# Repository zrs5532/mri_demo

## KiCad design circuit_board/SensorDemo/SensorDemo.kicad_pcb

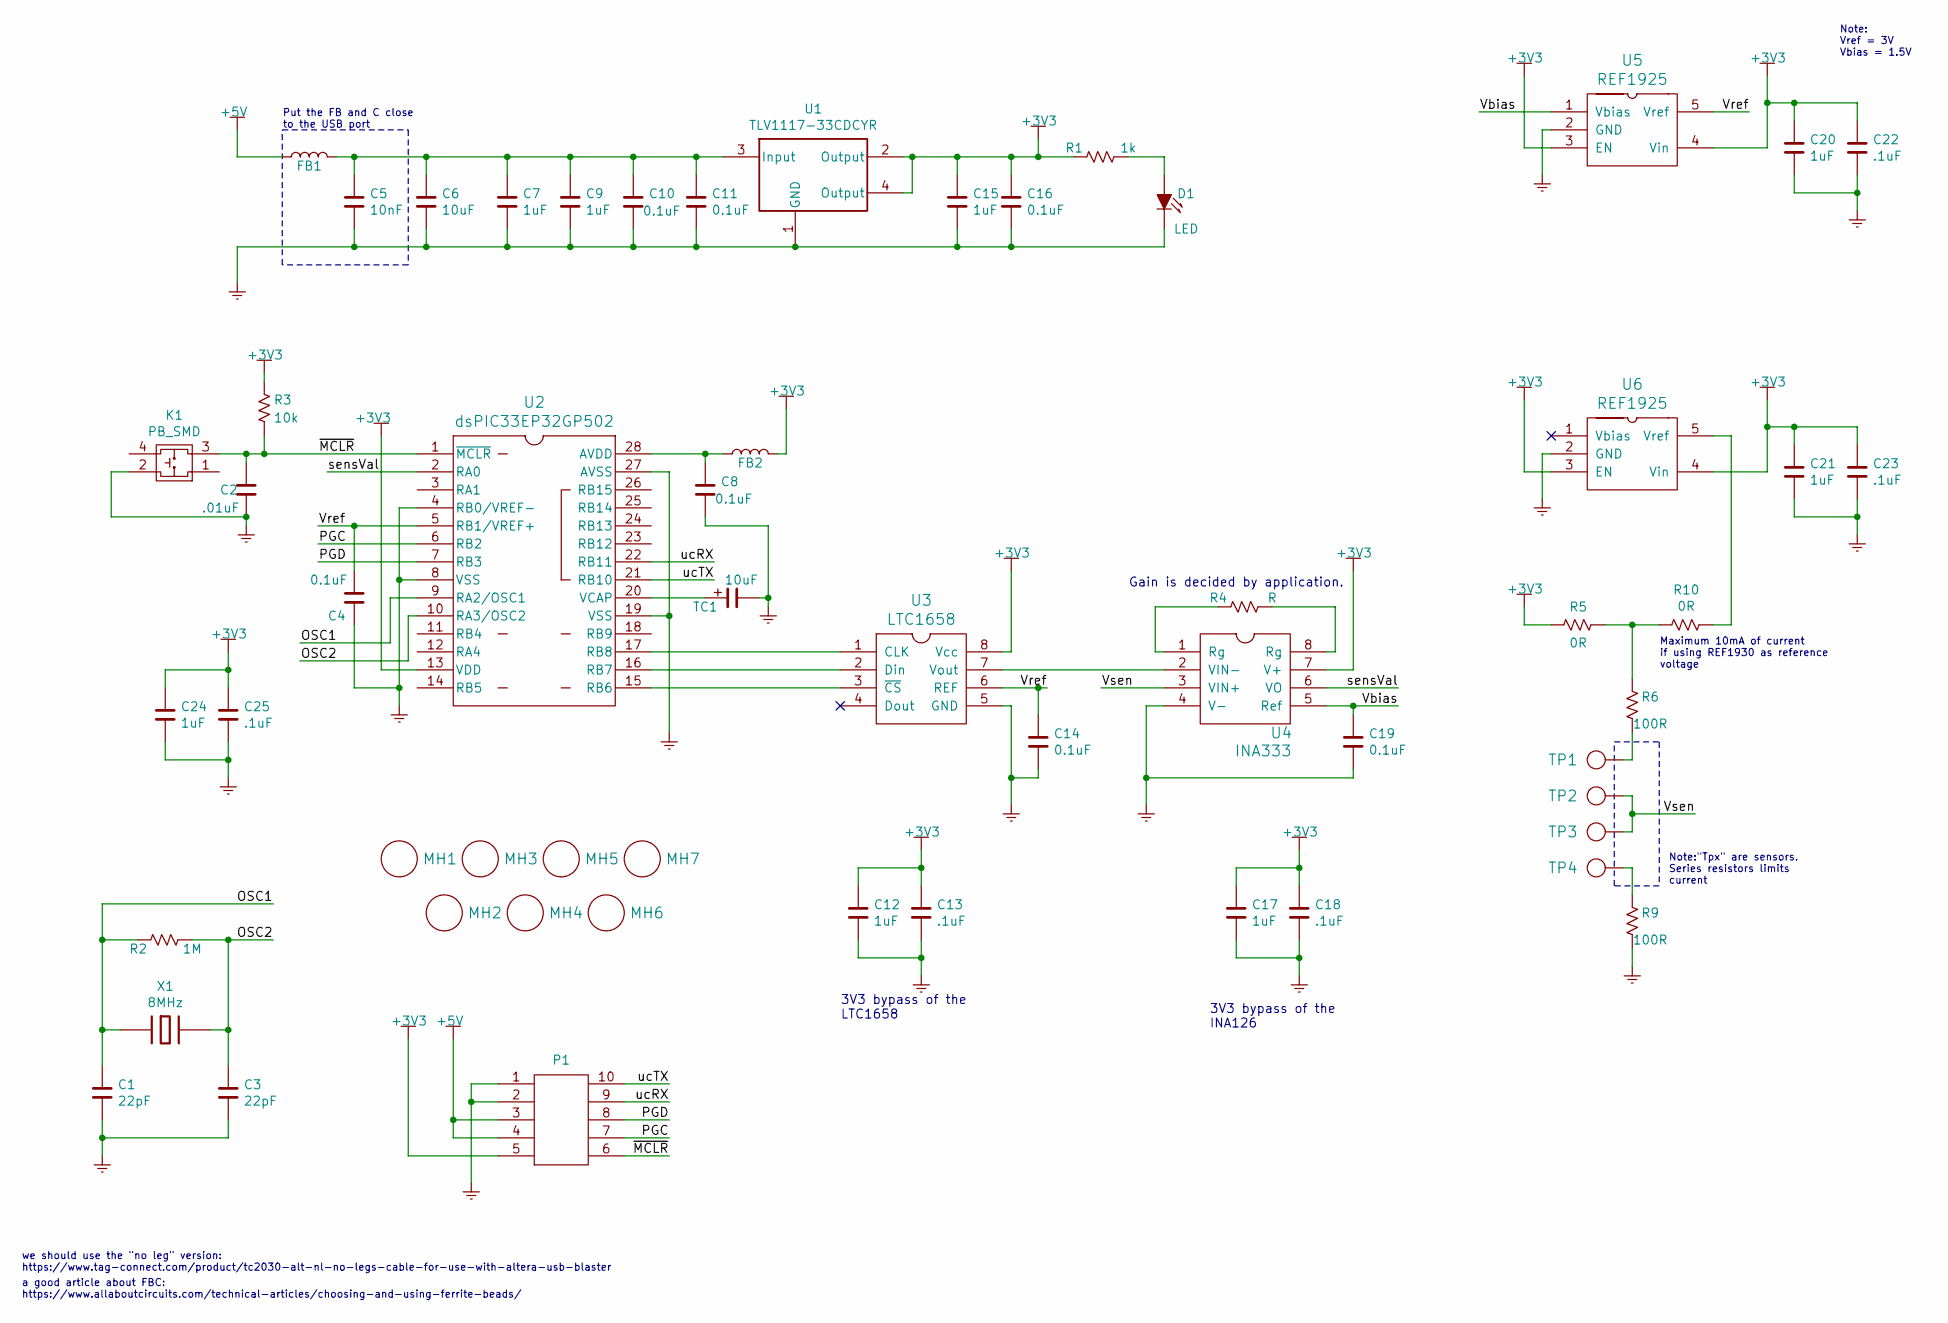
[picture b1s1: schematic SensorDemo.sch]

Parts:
C1, C3: 22pF; C0805
C2: .01uF; C0805
C4, C8, C10, C11, C14, C16, C19: 0.1uF; C0805
C5: 10nF; C0805
C6: 10uF; C0805
C7, C9, C12, C15, C17, C20, C21, C24: 1uF; C0805
C13, C18, C22, C23, C25: .1uF; C0805
D1: LED; LED0805
FB1, FB2: 12.3071 nano ohm; R0805
K1: PB_SMD; Key_SMD
MH1, MH2, MH3, MH4, MH5, MH6, MH7: MH; MH_3MM
P1: TC2050_IDC_NL; TC2050
R1: 1k; R0805
R2: 1M; R0805
R3: 10k; R0805
R4: R; R0805
R5, R10: 0R; R0805
R6, R9: 100R; R0805
TC1: 10uF; C1210
TP1, TP2, TP3, TP4: TP; TP_SMD_2MM
U1: TLV1117-33CDCYR; SOT-223
U2: dsPIC33EP32GP502; SOIC-28
U3: LTC1658; SOIC-8
U4: INA333; MSOP-8
U5, U6: REF1925; SOT-23-5
X1: 8MHz; CRYSTAL_ABM3-8.000MHz-D2Y-T

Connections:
+3V3: C12.1, C13.1, C15.1, C16.1, C17.1, C18.1, C20.1, C21.1, C22.1, C23.1, C24.1, C25.1, FB2.2, P1.5, R1.1, R3.1, R5.1, U1.2 (Output), U1.4 (Output), U2.13 (VDD), U3.8 (Vcc), U4.7 (V+), U5.3 (EN), U5.4 (Vin), U6.3 (EN), U6.4 (Vin); also elsewhere on the board
+5V: FB1.1, P1.3, P1.4; also elsewhere on the board
/OSC1: C1.1, R2.1, U2.9 (RA2/OSC1), X1.1
/OSC2: C3.1, R2.2, U2.10 (RA3/OSC2), X1.2
/PGC: P1.7, U2.6 (RB2)
/PGD: P1.8, U2.7 (RB3)
/Vbias: C19.1, U4.5 (Ref), U5.1 (Vbias)
/Vref: C4.1, C14.1, U2.5 (RB1/VREF+), U3.6 (REF), U5.5 (Vref)
/Vsen: TP2.1, TP3.1, U4.3 (VIN+); also elsewhere on the board
/sensVal: U2.2 (RA0), U4.6 (VO); also elsewhere on the board
/ucRX: P1.9, U2.22 (RB11)
/ucTX: P1.10, U2.21 (RB10)
/~MCLR: C2.1, K1.3, P1.6, R3.2, U2.1 (~MCLR)
GND: C1.2, C2.2, C3.2, C4.2, C5.2, C6.2, C7.2, C8.2, C9.2, C10.2, C11.2, C12.2, C13.2, C14.2, C15.2, C16.2, C17.2, C18.2, C19.2, C20.2, C21.2, C22.2, C23.2, C24.2, C25.2, D1.2 (K), K1.2, P1.1, P1.2, R9.2, TC1.2, U1.1 (GND), U2.4 (RB0/VREF-), U2.8 (VSS), U2.19 (VSS), U2.27 (AVSS), U3.5 (GND), U4.4 (V-), U5.2 (GND), U6.2 (GND)
unnamed: C8.1, FB2.1, U2.28 (AVDD)
unnamed: C5.1, C6.1, C7.1, C9.1, C10.1, C11.1, FB1.2, U1.3 (Input)
unnamed: D1.1 (A), R1.2
unnamed: R4.1, U4.1 (Rg)
unnamed: R4.2, U4.8 (Rg)
unnamed: R6.2, TP1.1
unnamed: R9.1, TP4.1
unnamed: R5.2, R6.1, R10.1
unnamed: R10.2, U6.5 (Vref)
unnamed: TC1.1, U2.20 (VCAP)
unnamed: U2.15 (RB6), U3.3 (~CS)
unnamed 25: U2.16 (RB7), U3.2 (Din); also elsewhere on the board
unnamed 26: U2.17 (RB8), U3.1 (CLK); also elsewhere on the board
unnamed 27: U3.7 (Vout), U4.2 (VIN-); also elsewhere on the board

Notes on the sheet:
Note: Vref = 3V Vbias = 1.5V
Put the FB and C close to the USB port
a good article about FBC: https://www.allaboutcircuits.com/technical-articles/choosing-and-using-ferrite-beads/
Gain is decided by application.
3V3 bypass of the LTC1658
3V3 bypass of the INA126
Maximum 10mA of current if using REF1930 as reference voltage
Note:"Tpx" are sensors. Series resistors limits current
we should use the "no leg" version: https://www.tag-connect.com/product/tc2030-alt-nl-no-legs-cable-for-use-with-altera-usb-blaster

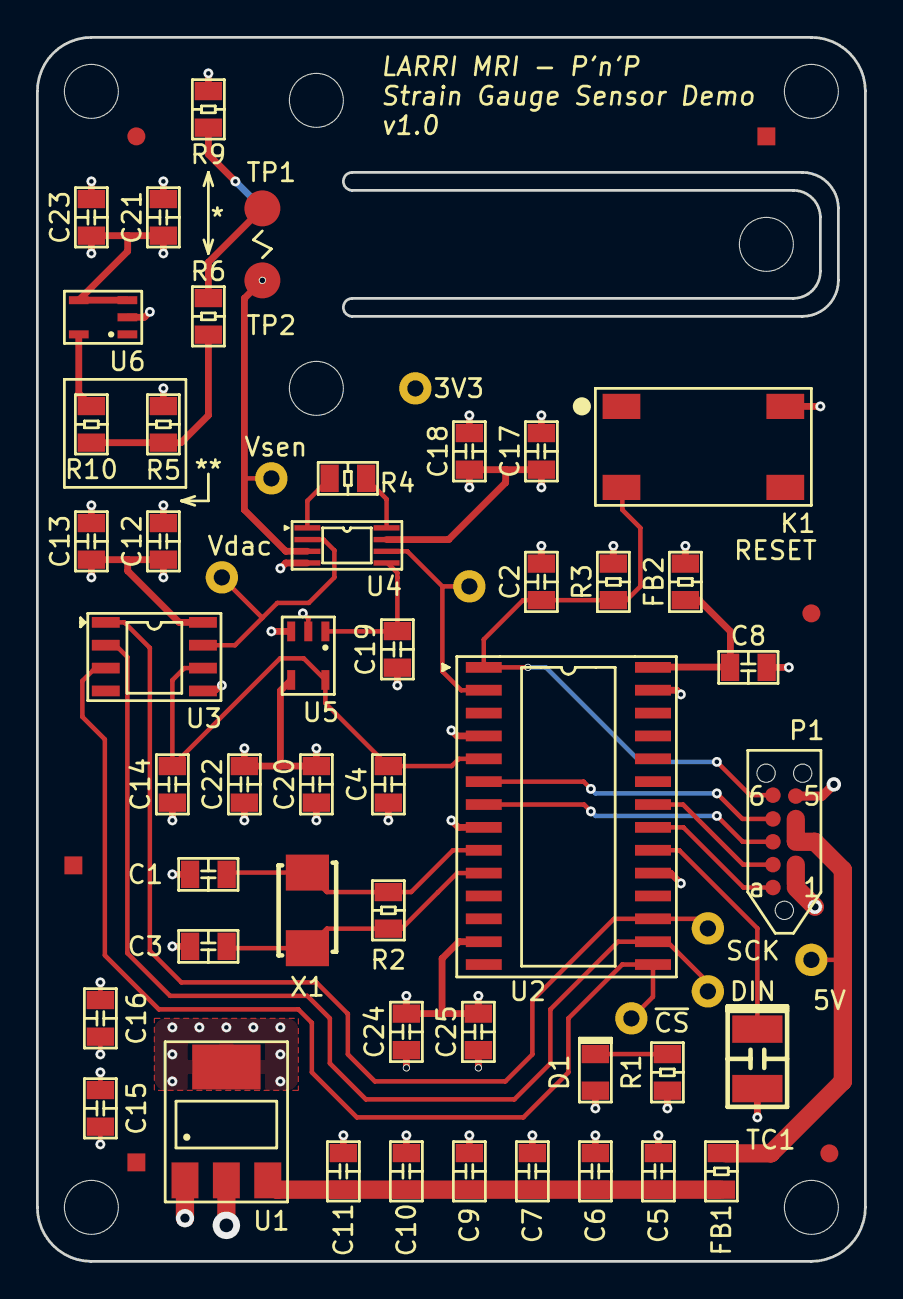
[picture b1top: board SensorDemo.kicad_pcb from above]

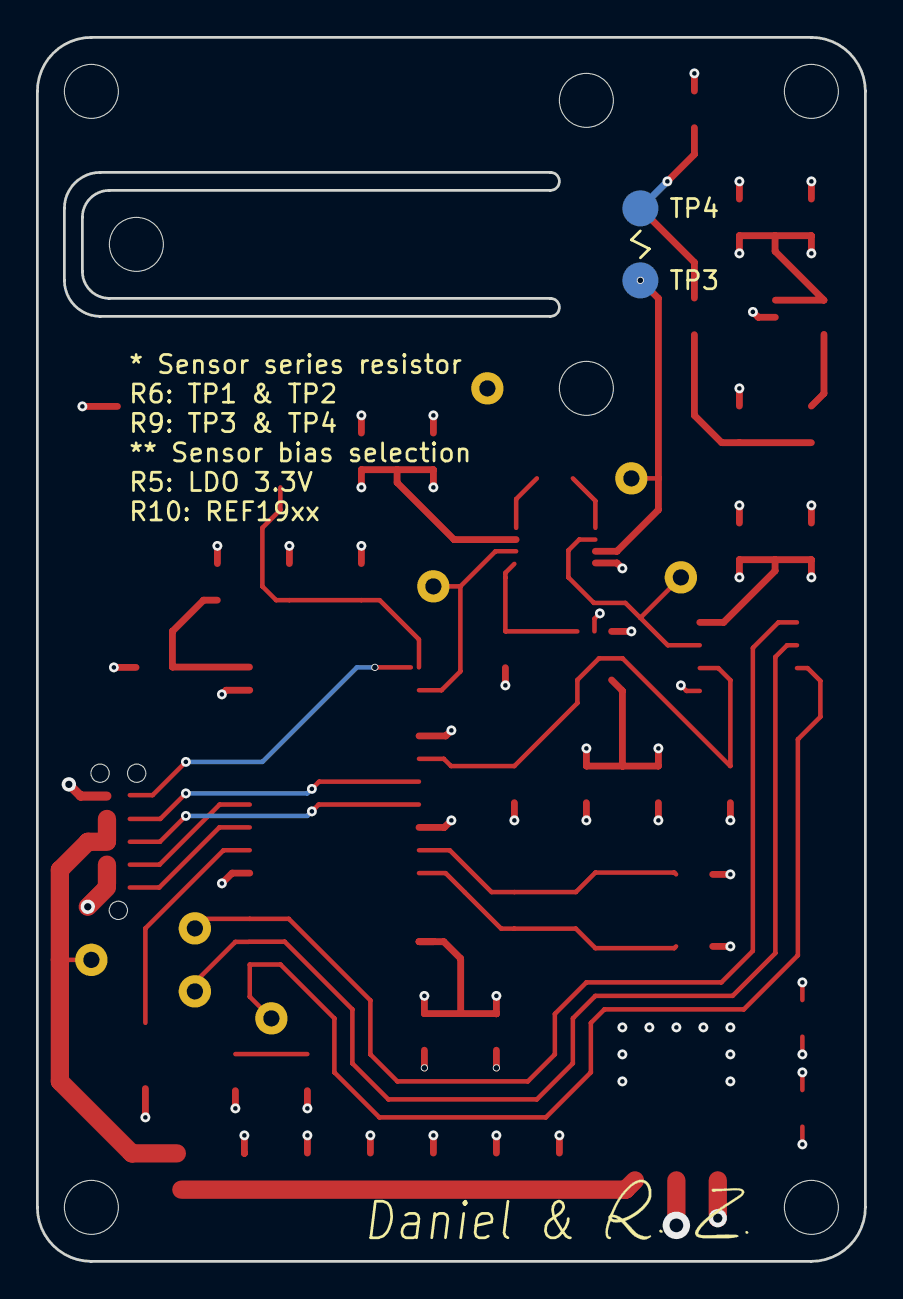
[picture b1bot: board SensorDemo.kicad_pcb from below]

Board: 4 copper layers, 46.0 x 68.0 mm, 70 parts (2 on the bottom side), 28 nets.

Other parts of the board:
3V3, 5V: TP_TH
DIN: TP_TH
FD: Val**; FD_1MM_CR
FD#2, FD#3, FD#5: Val**; FD_1MM_SQ
FD#4, FD#6: Val**; FD_1MM_CR
SCK: TP_TH
Vdac: TP_TH
Vsen: TP_TH
sensVal: TP_TH

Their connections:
+3V3: 3V3.1; also elsewhere on the board
+5V: 5V.1; also elsewhere on the board
/Vsen: Vsen.1; also elsewhere on the board
/sensVal: sensVal.1; also elsewhere on the board
unnamed 25: DIN.1; also elsewhere on the board
unnamed 26: SCK.1; also elsewhere on the board
unnamed 27: Vdac.1; also elsewhere on the board

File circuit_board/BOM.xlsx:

Component | Description | Link | Quantity
C1, C3 | 22pF | https://www.mouser.com/ProductDetail/KEMET/C0805C220K3HACTU?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 | 100
C2, C5, C6 | 0.01uF | https://www.mouser.com/ProductDetail/AVX/08051C103KAT2A?qs=K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 | 100
C4, C8, C10, C11, C13, C14, C16, C18, C19, C22, C23, C25 | 0.1uF | https://www.mouser.com/ProductDetail/AVX/08055C104KAT2A?qs=s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 | 100
C7, C9, C12, C15, C17, C20, C21, C24 | 1uF | https://www.mouser.com/ProductDetail/Samsung-Electro-Mechani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 | 100
FB1, FB2 | 12.3071 nano Ohm | https://www.mouser.com/ProductDetail/Fair-Rite/2508051027Y1?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 | 100
K1 | Push Button | https://www.mouser.com/ProductDetail/E-Switch/LL3301NF065QG/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 | 25
R1 | 1k Ohm | https://www.mouser.com/ProductDetail/Vishay-Dale/CRCW08051K0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 | 100
R2 | 1M Ohm | https://www.mouser.com/ProductDetail/Vishay-Dale/CRCW08051M0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 | 100
R3 | 10k Ohm | https://www.mouser.com/ProductDetail/Bourns/CR0805-FX-1003EL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 | 100
R6, R9 | 100 Ohm | https://www.mouser.com/ProductDetail/Vishay-Dale/CRCW0805100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 | 100
TC1 | 10uF | https://www.mouser.com/ProductDetail/AVX/TAJA106K010RNJV?qs=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 | 20
U1 | LDO - TLV1117-33CDCYR | https://www.mouser.com/ProductDetail/STMicroelectronics/LDL1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 | 20
U2 | dsPIC33EP32GP502 | https://www.mouser.com/ProductDetail/Microchip-Technology/ds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 | 5
U3 | DAC - LTC1659 | https://www.mouser.com/ProductDetail/Analog-Devices/LTC1659C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 | 5
 | LTC 1655L | https://www.mouser.com/ProductDetail/Analog-Devices/LTC1655L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 | 3
 | LED | https://www.mouser.com/ProductDetail/Kingbright/APT2012SRCPR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 | 10
 | 0R | https://www.mouser.com/ProductDetail/Yageo/RC0805JR-070RL?qs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 | 100
 | IDC | https://www.mouser.com/ProductDetail/Wurth-Elektronik/612010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 | 5
 | uart bridge | https://www.mouser.com/ProductDetail/SparkFun/BOB-13263?qs=w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 | 3
 | tag-cable | https://www.tag-connect.com/product/tc2050-idc-nl-10-pin-no-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 | 1
stunts | SOIC8 | https://www.mouser.com/ProductDetail/STMicroelectronics/LM35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 | 10
 | MSOP8 | https://www.mouser.com/ProductDetail/NJR/NJM2904CARB1-TE1?qs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 | 10
 | SOIC28 | https://www.mouser.com/ProductDetail/Microchip-Technology/PI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 | 10
 | SOT23-5 | https://www.mouser.com/ProductDetail/Microchip-Technology-Mi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 | 10
 | SOT223 | https://www.mouser.com/ProductDetail/Nexperia/PMT560ENEAX?qs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 | 10

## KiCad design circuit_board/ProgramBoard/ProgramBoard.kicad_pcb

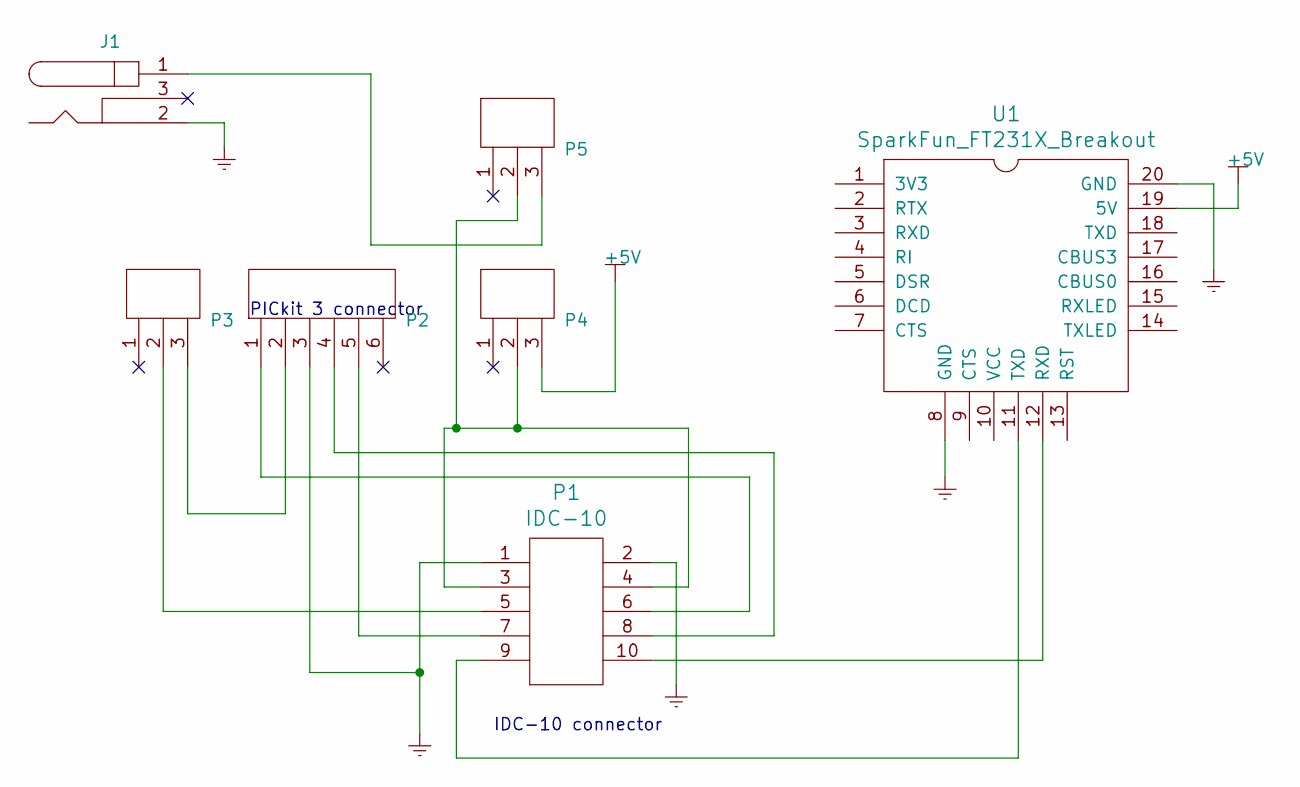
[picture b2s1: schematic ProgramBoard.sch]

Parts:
J1: BARREL_JACK
P1: IDC-10; IDC_10
P2: HEADER_6
P3, P4, P5: HEADER_3
U1: SparkFun_FT231X_Breakout

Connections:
+5V: P4.3, U1.19 (5V)
GND: J1.2, P1.1, P1.2, P2.3, U1.8 (GND), U1.20 (GND)
unnamed: J1.1, P5.3
unnamed: P1.3, P1.4, P4.2, P5.2
unnamed: P1.5, P3.2
unnamed: P1.6, P2.1
unnamed: P1.7, P2.5
unnamed: P1.8, P2.4
unnamed: P1.9, U1.11 (TXD)
unnamed: P1.10, U1.12 (RXD)
unnamed: P2.2, P3.3

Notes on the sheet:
PICkit 3 connector
IDC-10 connector

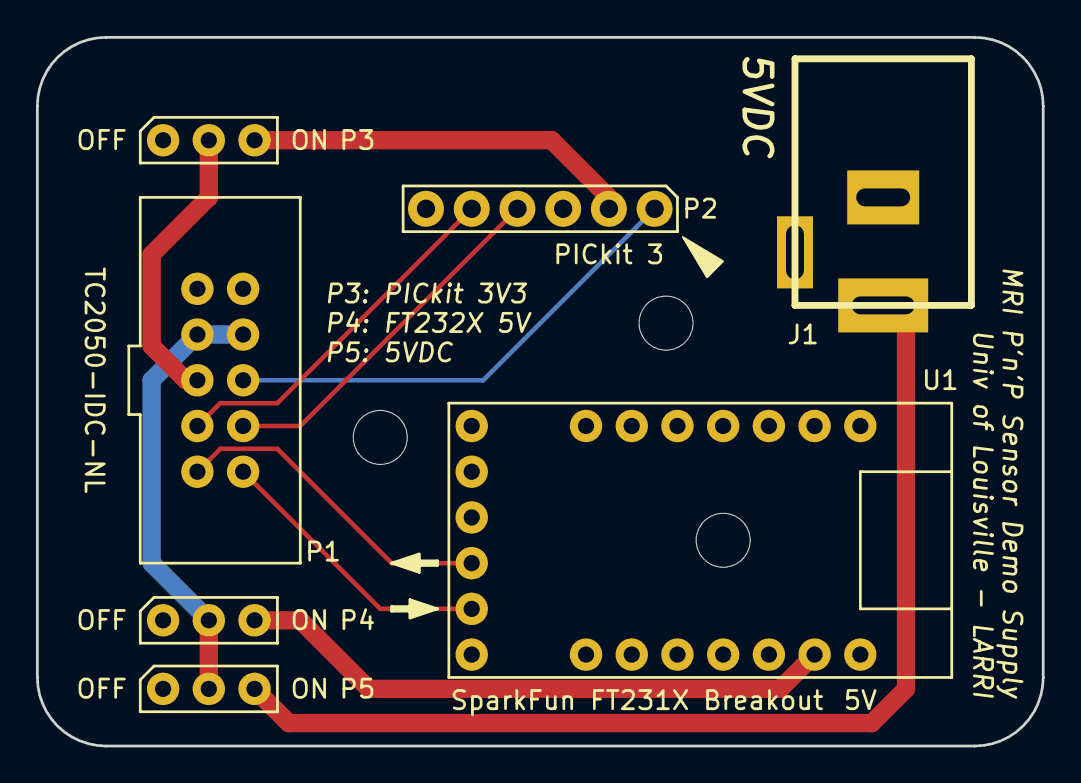
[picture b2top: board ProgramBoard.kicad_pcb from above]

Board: 2 copper layers, 55.9 x 39.4 mm, 10 parts (0 on the bottom side), 11 nets.

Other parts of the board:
MH3, MH3#2, MH3#3: MH; MH_3MM

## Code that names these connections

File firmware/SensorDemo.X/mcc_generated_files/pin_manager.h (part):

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*/
/**
  @Summary
    Sets the GPIO pin, RA0, high using LATA0.

  @Description
    Sets the GPIO pin, RA0, high using LATA0.

  @Preconditions
    The RA0 must be set to an output.
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#define channel_AN0_SetHigh()          (_LATA0 = 1)
/**
  @Summary
    Sets the GPIO pin, RA0, low using LATA0.

  @Description
    Sets the GPIO pin, RA0, low using LATA0.

  @Preconditions
    The RA0 must be set to an output.
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#define channel_AN0_SetLow()           (_LATA0 = 0)
/**
  @Summary
    Toggles the GPIO pin, RA0, using LATA0.

  @Description
    Toggles the GPIO pin, RA0, using LATA0.

  @Preconditions
    The RA0 must be set to an output.
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#define channel_AN0_Toggle()           (_LATA0 ^= 1)
/**
  @Summary
    Reads the value of the GPIO pin, RA0.

  @Description
    Reads the value of the GPIO pin, RA0.

  @Preconditions
    None.
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    </code>

*/
#define channel_AN0_GetValue()         _RA0
/**
  @Summary
    Configures the GPIO pin, RA0, as an input.

  @Description
    Configures the GPIO pin, RA0, as an input.

  @Preconditions
    None.
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#define channel_AN0_SetDigitalInput()  (_TRISA0 = 1)
/**
  @Summary
    Configures the GPIO pin, RA0, as an output.

  @Description
    Configures the GPIO pin, RA0, as an output.

  @Preconditions
    None.
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#define channel_AN0_SetDigitalOutput() (_TRISA0 = 0)
/**
  @Summary
    Sets the GPIO pin, RB6, high using LATB6.

  @Description
    Sets the GPIO pin, RB6, high using LATB6.

  @Preconditions
    The RB6 must be set to an output.
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#define CS1_SetHigh()          (_LATB6 = 1)
/**
  @Summary
    Sets the GPIO pin, RB6, low using LATB6.

  @Description
    Sets the GPIO pin, RB6, low using LATB6.

  @Preconditions
    The RB6 must be set to an output.
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#define CS1_SetLow()           (_LATB6 = 0)
/**
  @Summary
    Toggles the GPIO pin, RB6, using LATB6.

  @Description
    Toggles the GPIO pin, RB6, using LATB6.

  @Preconditions
    The RB6 must be set to an output.
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#define CS1_Toggle()           (_LATB6 ^= 1)
/**
  @Summary
    Reads the value of the GPIO pin, RB6.

  @Description
    Reads the value of the GPIO pin, RB6.

  @Preconditions
    None.
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    </code>

*/
#define CS1_GetValue()         _RB6
/**
  @Summary
    Configures the GPIO pin, RB6, as an input.

  @Description
    Configures the GPIO pin, RB6, as an input.

  @Preconditions
    None.
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#define CS1_SetDigitalInput()  (_TRISB6 = 1)
/**
  @Summary
    Configures the GPIO pin, RB6, as an output.

  @Description
    Configures the GPIO pin, RB6, as an output.

  @Preconditions
    None.
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#define CS1_SetDigitalOutput() (_TRISB6 = 0)
/**
  @Summary
    Sets the GPIO pin, RB7, high using LATB7.

  @Description
    Sets the GPIO pin, RB7, high using LATB7.

  @Preconditions
    The RB7 must be set to an output.
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#define SDO2_SetHigh()          (_LATB7 = 1)
/**
  @Summary
    Sets the GPIO pin, RB7, low using LATB7.

  @Description
    Sets the GPIO pin, RB7, low using LATB7.

  @Preconditions
    The RB7 must be set to an output.
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#define SDO2_SetLow()           (_LATB7 = 0)
/**
  @Summary
    Toggles the GPIO pin, RB7, using LATB7.

  @Description
    Toggles the GPIO pin, RB7, using LATB7.

  @Preconditions
    The RB7 must be set to an output.
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#define SDO2_Toggle()           (_LATB7 ^= 1)
/**
  @Summary
    Reads the value of the GPIO pin, RB7.

  @Description
    Reads the value of the GPIO pin, RB7.

  @Preconditions
    None.
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    </code>

*/
#define SDO2_GetValue()         _RB7
/**
  @Summary
    Configures the GPIO pin, RB7, as an input.

  @Description
    Configures the GPIO pin, RB7, as an input.

  @Preconditions
    None.
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#define SDO2_SetDigitalInput()  (_TRISB7 = 1)
/**
  @Summary
    Configures the GPIO pin, RB7, as an output.

  @Description
    Configures the GPIO pin, RB7, as an output.

  @Preconditions
    None.
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#define SDO2_SetDigitalOutput() (_TRISB7 = 0)
/**
  @Summary
    Sets the GPIO pin, RB8, high using LATB8.

  @Description
    Sets the GPIO pin, RB8, high using LATB8.

  @Preconditions
    The RB8 must be set to an output.
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#define SCK2OUT_SetHigh()          (_LATB8 = 1)
/**
  @Summary
    Sets the GPIO pin, RB8, low using LATB8.

  @Description
    Sets the GPIO pin, RB8, low using LATB8.

  @Preconditions
    The RB8 must be set to an output.
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#define SCK2OUT_SetLow()           (_LATB8 = 0)
/**
  @Summary
    Toggles the GPIO pin, RB8, using LATB8.

  @Description
    Toggles the GPIO pin, RB8, using LATB8.

  @Preconditions
    The RB8 must be set to an output.
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#define SCK2OUT_Toggle()           (_LATB8 ^= 1)
/**
  @Summary
    Reads the value of the GPIO pin, RB8.

  @Description
    Reads the value of the GPIO pin, RB8.

  @Preconditions
    None.
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    </code>

*/
#define SCK2OUT_GetValue()         _RB8
/**
  @Summary
    Configures the GPIO pin, RB8, as an input.

  @Description
    Configures the GPIO pin, RB8, as an input.

  @Preconditions
    None.
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#define SCK2OUT_SetDigitalInput()  (_TRISB8 = 1)
/**
  @Summary
    Configures the GPIO pin, RB8, as an output.

  @Description
    Configures the GPIO pin, RB8, as an output.

  @Preconditions
    None.
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
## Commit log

2021-02-04 repository created
2021-02-05 local schematic library renamed
2021-02-06 test fron Dan
2021-02-09 real circuit board design added
    circuit design under "circuit_board/SensorDemo", project library added under "circuit_board/library"
2021-02-09 testing project under "circuit_board" is removed.
2021-02-09 uploaded mplab code
2021-02-10 updated schematic & footprints
2021-02-10 relocate the SensorDemo.x project into "firmware" folder
    nothing else has been changed.
2021-02-10 schematic comments made
    minor updates:
    edited schematic library to make some parts look better
2021-02-11 schematic changes
2021-02-11 add some comments
2021-02-11 updated schematic
2021-02-13 updated firmware
2021-02-14 schematic edited
    1. Let's use another REF1930 to bias the sensors. limit current to 15mA (20mA maximum) for safe operation.
    2. FBC filter added to AVDD pin. value FB value needed.
    3. sensor circuit included, with the position of two current limiting resistors.
    4. bypass and decouple caps are added to INA & DAC power lines.
    5. to Daniel: please add crystal circuit to the MCU, and finish the FT232 circuit.
2021-02-15 Create Notes.txt
    a text file "Notes.txt" is created to document design notes and ideas.
2021-02-16 minor update
    ft231 breakout board added under reference folder.
    minor update on schematic.
2021-02-17 updated schematic
    added footprints to everything and minor changes to 6pin
2021-02-18 updates in firmware
    attempted to implement interrupt calibration
2021-02-19 updated schematic
    added footprints & created footprint for connector
2021-02-22 update schematic
    pcb parts in place. need to connect traces
2021-02-22 minor change on schematic
    please add pads to the 6 pin connector.
2021-02-23 updated schematic
    -spaced parts
    -filled ground layer
    -added vias
2021-02-23 symbol and pcb footprint updated
    Added test points to replace the sensors.
    TC2030 part modified.
    the button needs modification.
    TG connector:
    https://www.tag-connect.com/product/tc2030-alt-nl-no-legs-cable-for-use-with-altera-usb-blaster
2021-02-24 updated schematic
    -fixed footprints
    -spread parts
    -connected some traces
    - found FB (1kOhm, 1A)
2021-02-25 update pcb
    -connected traces
2021-02-25 PCB edited
2021-02-26 completed ProgramBoard
2021-02-27 SensorDemo board updated
    re-positioned all components and routed pcb.
2021-02-27 key needs revise
    check the button's footprint.
2021-02-28 examined the program board
    try to switch to 10 pin tag cable to combine the programmer, UART, and power.
2021-03-01 SensorDemo and Program board modified
    1. SensorDemo board minor adjustment, 3D models added.
    2. the TC2050 cable is added and routed on programmer board.
    3. 3D models are added into the library.
2021-03-05 firmware update
    polling calibration
2021-03-05 updated button footprint
2021-03-07 update firmware
2021-03-09 updated code
    -tried implementing p controller
2021-03-09 reset key modified
2021-03-09 updated SensoDemo and ProgramBoard
    INA126 is replaced by INA333.
    TC2050-IDC-NL cable will be used for powering and programming.
    both boards should be done.
2021-03-10 updated schematic
    -fixed programming board 5v
2021-03-10 testing pins added
    updated PCB design:
    added testing pins on the SensorDemo.
    ProgramBoard modified GND connections.
2021-03-10 modified according to Doug
    on SensorDemo, fiducial marks are added, via size changed to .25mm and .55mm, decreased solder mask gap between pins on MSOP8 package.
    the minimum JLC can take between pins is .2mm for green mask.
2021-03-12 PCB fabrication file generated
    the PCBs are sent to JLC for fabrication, gerber files created.
2021-03-13 firmware change
    - cleaned up code
    - changed calibration structure
2021-03-16 updated firmware
    -improved accuracy of calibration
2021-03-16 Revert "Merge branch 'master' of https://github.com/zrs5532/mri_demo"
    This reverts commit b0c8028f714b16f114d60085c0a86ac2043fc740, reversing
    changes made to 0fccd9f34ae5c363ed48057d6b873a7540cc24aa.
2021-03-16 Revert "Revert "Merge branch 'master' of https://github.com/zrs5532/mri_demo""
    This reverts commit c7bcd66b67d9c03c78e75f611b5453059c538dec.
2021-03-17 added BOM
2021-03-17 Updated BOM
    BOM is edited so ready to purchase the part. Right now, LTC1658 is not available anywhere (mouser/digikey), so LTC1659 (12-bit) and LTC1655L (16-bit) are ordered instead.
    parts marked as "stunts" are for practice purpose.
2021-03-17 firmware changes
    12bit testing & tuning
2021-04-06 calibration change
2021-04-07 calibration fix
    -finally works
    -can make bit faster
    -clean up code (debug)
2021-04-08 Update Firmware
    -Added Comments
    -Made Calibration faster
2021-04-13 Uploaded Report
2021-04-14 comments to the report
    some comments to the report are added.
2021-04-20 paper update
2021-04-21 report done
2021-08-11 updated fiducial marks

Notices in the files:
firmware/SensorDemo.X/mcc_generated_files/pin_manager.h:
(c) 2020 Microchip Technology Inc. and its subsidiaries. You may use this
